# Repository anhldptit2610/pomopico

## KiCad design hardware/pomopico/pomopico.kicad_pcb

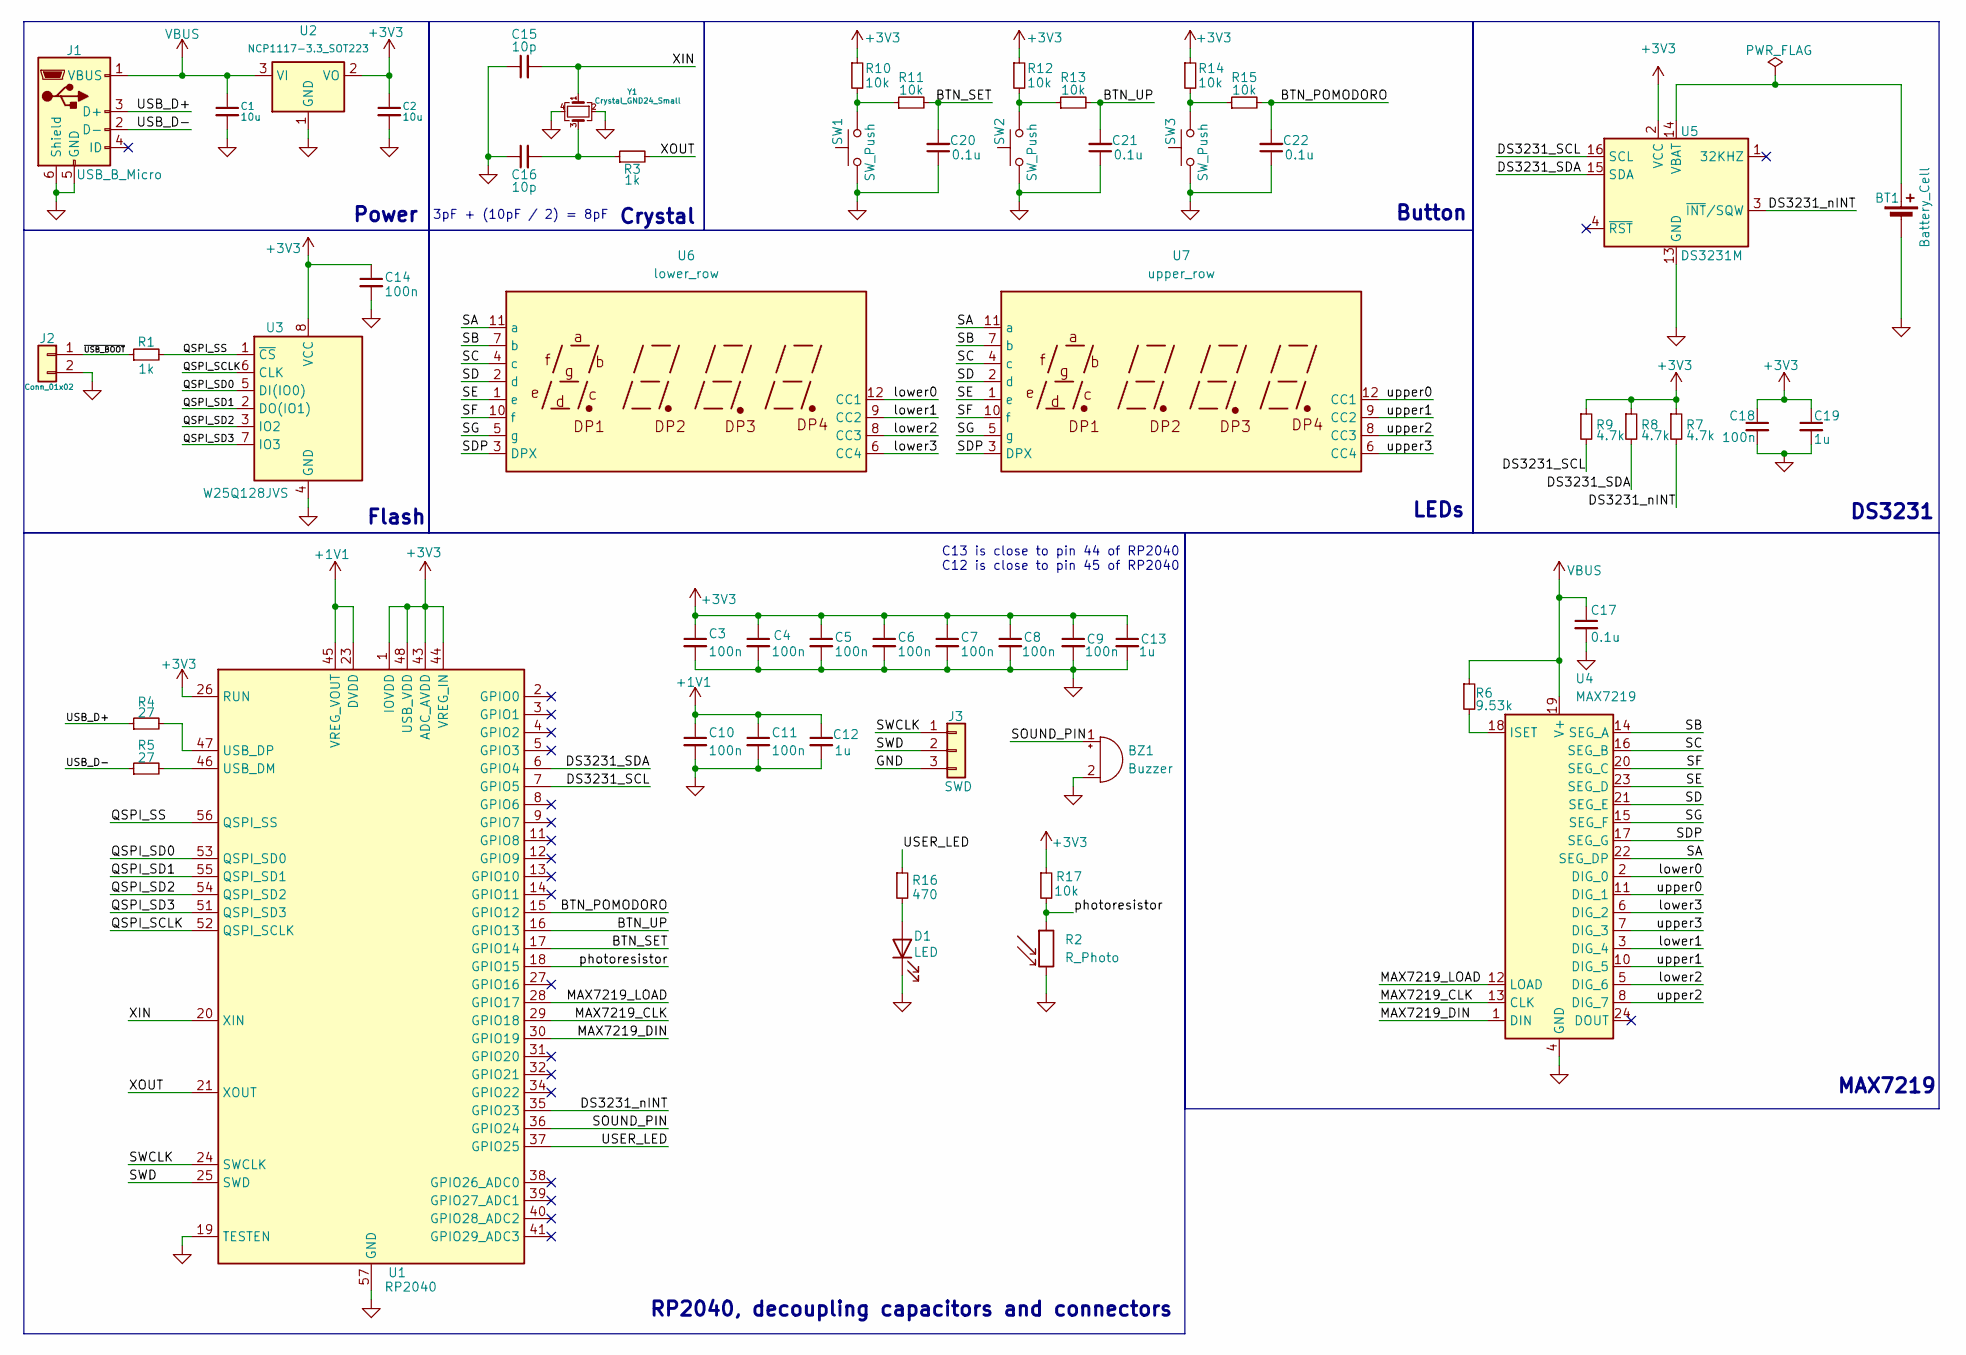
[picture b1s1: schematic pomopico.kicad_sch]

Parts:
BT1: Battery_Cell; Battery_Panasonic_CR2032-HFN_Horizontal_CircularHoles
BZ1: Buzzer; Buzzer_12x9.5RM7.6
C1, C2: 10u; C_0402_1005Metric_Pad0.74x0.62mm_HandSolder
C3, C4, C5, C6, C7, C8, C9, C10, C11, C14, C18: 100n; C_0402_1005Metric_Pad0.74x0.62mm_HandSolder
C12, C13, C19: 1u; C_0402_1005Metric_Pad0.74x0.62mm_HandSolder
C15, C16: 10p; C_0402_1005Metric_Pad0.74x0.62mm_HandSolder
C17, C20, C21, C22: 0.1u; C_0402_1005Metric_Pad0.74x0.62mm_HandSolder
D1: LED; LED_0603_1608Metric_Pad1.05x0.95mm_HandSolder
J1: USB_B_Micro; USB_Micro-B_Molex-105017-0001
J2: Conn_01x02; PinHeader_1x02_P2.54mm_Vertical
J3: SWD; PinHeader_1x03_P2.54mm_Vertical
R1: 1k; R_0603_1608Metric_Pad0.98x0.95mm_HandSolder
R2: R_Photo; PHODET_PDV-P8103
R3: 1k; R_0402_1005Metric_Pad0.72x0.64mm_HandSolder
R4, R5: 27; R_0402_1005Metric_Pad0.72x0.64mm_HandSolder
R6: 9.53k; R_0402_1005Metric_Pad0.72x0.64mm_HandSolder
R7, R8, R9: 4.7k; R_0402_1005Metric_Pad0.72x0.64mm_HandSolder
R10, R11, R12, R13, R14, R15, R17: 10k; R_0402_1005Metric_Pad0.72x0.64mm_HandSolder
R16: 470; R_0402_1005Metric_Pad0.72x0.64mm_HandSolder
SW1, SW2, SW3: SW_Push; SW_Tactile_SPST_Angled_PTS645Vx83-2LFS
U1: RP2040; RP2040-QFN-56
U2: NCP1117-3.3_SOT223; SOT-223-3_TabPin2
U3: W25Q128JVS; SOIC-8_5.23x5.23mm_P1.27mm
U4: MAX7219; SOIC-24W_7.5x15.4mm_P1.27mm
U5: DS3231M; SOIC-16W_7.5x10.3mm_P1.27mm
U6: lower_row; CC56-12GWA
U7: upper_row; CC56-12GWA
Y1: Crystal_GND24_Small; Crystal_SMD_3225-4Pin_3.2x2.5mm

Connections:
+1V1: C10.1, C11.1, C12.1, U1.23 (DVDD), U1.45 (VREG_VOUT), U1.50 (DVDD)
+3V3: C2.1, C3.1, C4.1, C5.1, C6.1, C7.1, C8.1, C9.1, C13.1, C14.1, C18.1, C19.1, R7.1, R8.1, R9.1, R10.1, R12.1, R14.1, R17.1, U1.1 (IOVDD), U1.10 (IOVDD), U1.22 (IOVDD), U1.26 (RUN), U1.33 (IOVDD), U1.42 (IOVDD), U1.43 (ADC_AVDD), U1.44 (VREG_IN), U1.48 (USB_VDD), U1.49 (IOVDD), U2.2 (VO), U3.8 (VCC), U5.2 (VCC)
/BTN_POMODORO: C22.2, R15.2, U1.15 (GPIO12)
/BTN_SET: C20.2, R11.2, U1.17 (GPIO14)
/BTN_UP: C21.2, R13.2, U1.16 (GPIO13)
/DS3231_SCL: R9.2, U1.7 (GPIO5), U5.16 (SCL)
/DS3231_SDA: R8.2, U1.6 (GPIO4), U5.15 (SDA)
/DS3231_nINT: R7.2, U1.35 (GPIO23), U5.3 (~INT/SQW)
/MAX7219_CLK: U1.29 (GPIO18), U4.13 (CLK)
/MAX7219_DIN: U1.30 (GPIO19), U4.1 (DIN)
/MAX7219_LOAD: U1.28 (GPIO17), U4.12 (LOAD)
/QSPI_SCLK: U1.52 (QSPI_SCLK), U3.6 (CLK)
/QSPI_SD0: U1.53 (QSPI_SD0), U3.5 (DI(IO0))
/QSPI_SD1: U1.55 (QSPI_SD1), U3.2 (DO(IO1))
/QSPI_SD2: U1.54 (QSPI_SD2), U3.3 (IO2)
/QSPI_SD3: U1.51 (QSPI_SD3), U3.7 (IO3)
/QSPI_SS: R1.2, U1.56 (QSPI_SS), U3.1 (~CS)
/SA: U4.22 (SEG_DP), U6.11 (a), U7.11 (a)
/SB: U4.14 (SEG_A), U6.7 (b), U7.7 (b)
/SC: U4.16 (SEG_B), U6.4 (c), U7.4 (c)
/SD: U4.21 (SEG_E), U6.2 (d), U7.2 (d)
/SDP: U4.17 (SEG_G), U6.3 (DPX), U7.3 (DPX)
/SE: U4.23 (SEG_D), U6.1 (e), U7.1 (e)
/SF: U4.20 (SEG_C), U6.10 (f), U7.10 (f)
/SG: U4.15 (SEG_F), U6.5 (g), U7.5 (g)
/SOUND_PIN: BZ1.1 (+), U1.36 (GPIO24)
/SWCLK: J3.1, U1.24 (SWCLK)
/SWD: J3.2, U1.25 (SWD)
/USB_D+: J1.3 (D+), R4.1
/USB_D-: J1.2 (D-), R5.1
/USER_LED: R16.1, U1.37 (GPIO25)
/XIN: C15.2, U1.20 (XIN), Y1.1
/XOUT: R3.2, U1.21 (XOUT)
/lower0: U4.2 (DIG_0), U6.12 (CC1)
/lower1: U4.3 (DIG_4), U6.9 (CC2)
/lower2: U4.5 (DIG_6), U6.8 (CC3)
/lower3: U4.6 (DIG_2), U6.6 (CC4)
/photoresistor: R2.1, R17.2, U1.18 (GPIO15)
/upper0: U4.11 (DIG_1), U7.12 (CC1)
/upper1: U4.10 (DIG_5), U7.9 (CC2)
/upper2: U4.8 (DIG_7), U7.8 (CC3)
/upper3: U4.7 (DIG_3), U7.6 (CC4)
/~USB_BOOT: J2.1, R1.1
GND: BT1.2 (-), BZ1.2 (-), C1.2, C2.2, C3.2, C4.2, C5.2, C6.2, C7.2, C8.2, C9.2, C10.2, C11.2, C12.2, C13.2, C14.2, C15.1, C16.1, C17.2, C18.2, C19.2, C20.1, C21.1, C22.1, D1.1 (K), J1.5 (GND), J1.6 (Shield), J2.2, J3.3, R2.2, SW1.1, SW2.1, SW3.1, U1.19 (TESTEN), U1.57 (GND), U2.1 (GND), U3.4 (GND), U4.4 (GND), U4.9 (GND), U5.5 (GND), U5.6 (GND), U5.7 (GND), U5.8 (GND), U5.9 (GND), U5.10 (GND), U5.11 (GND), U5.12 (GND), U5.13 (GND), Y1.2, Y1.4
unnamed: BT1.1 (+), U5.14 (VBAT)
unnamed: C16.2, R3.1, Y1.3
unnamed: D1.2 (A), R16.2
unnamed: R10.2, R11.1, SW1.2
unnamed: R12.2, R13.1, SW2.2
unnamed: R14.2, R15.1, SW3.2
unnamed: R5.2, U1.46 (USB_DM)
unnamed: R4.2, U1.47 (USB_DP)
unnamed: R6.2, U4.18 (ISET)
VBUS: C1.1, C17.1, J1.1 (VBUS), R6.1, U2.3 (VI), U4.19 (V+)

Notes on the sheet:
MAX7219
Button
Crystal
3pF + (10pF / 2) = 8pF
C13 is close to pin 44 of RP2040 C12 is close to pin 45 of RP2040
DS3231
LEDs
Power
RP2040, decoupling capacitors and connectors
Flash

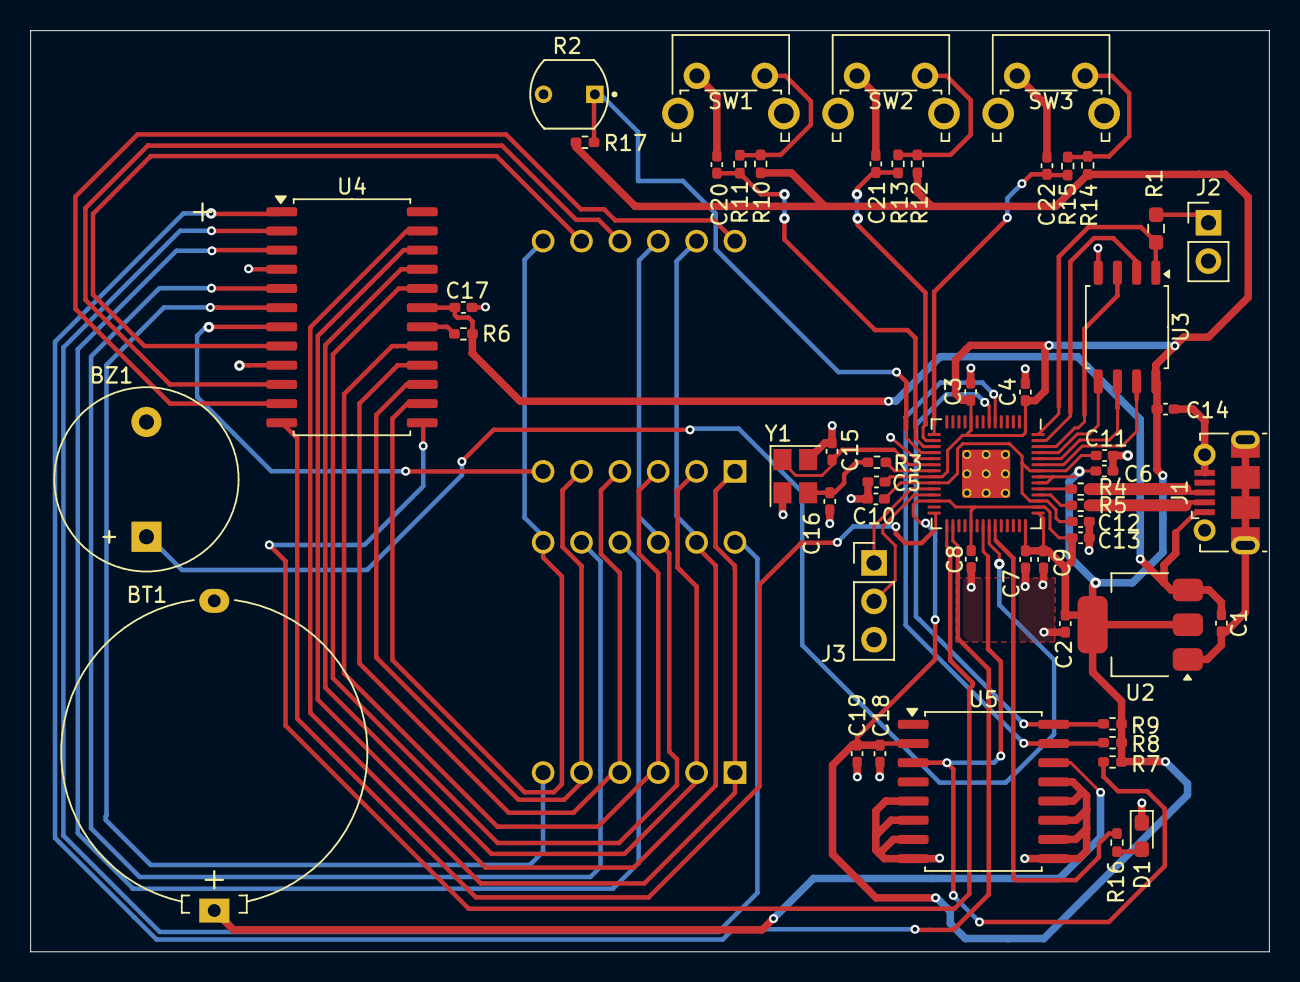
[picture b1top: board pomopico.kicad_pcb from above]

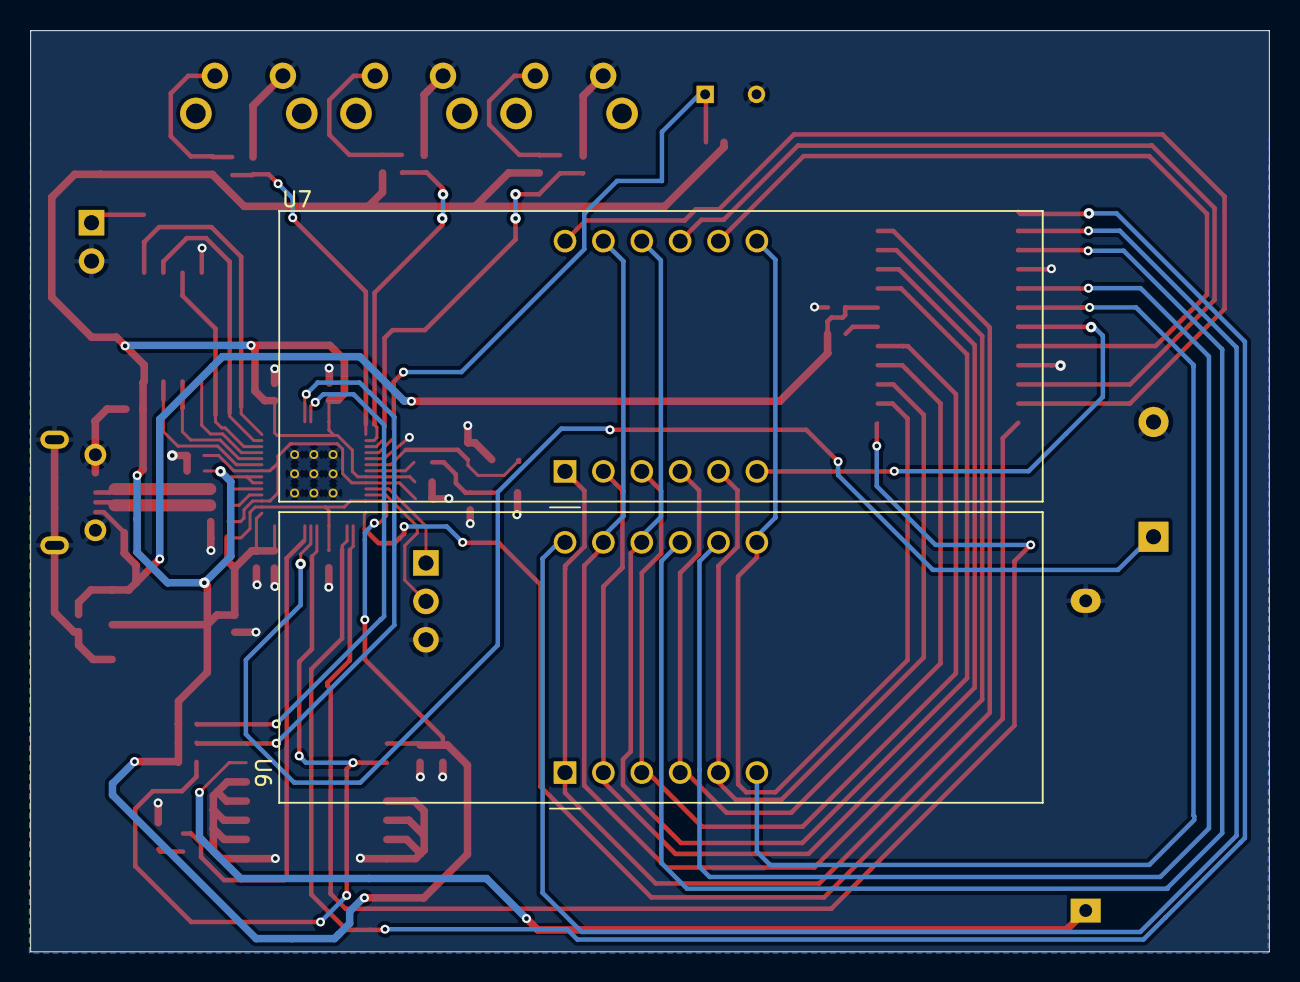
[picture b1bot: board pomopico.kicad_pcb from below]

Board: 2 copper layers, 82.0 x 61.0 mm, 56 parts (2 on the bottom side), 54 nets.

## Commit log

2024-06-01 ignore firmware/build
2024-06-02 add display code, but still very simple
2024-06-02 ignore /build folder
2024-06-02 DS1307 basically works(can show time correctly)
2024-06-03 clock now can config via buttons
2024-06-03 remove useless variables
2024-06-04 hourly chime done
2024-06-05 alarm now works perfectly
2024-06-05 now pomodoro goes online...
2024-06-05 fix the slow response of button SET when setting up alarm
2024-06-12 add hardware v0.1
2024-06-12 add info to pcb file
2024-06-12 pomodoro feature rework
